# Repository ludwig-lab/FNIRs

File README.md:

# FNIRs
This project aims to create a FNIRs device that will connect directly to the TDT. The current circuit boards in this repository include as follows:
Detector: This board includes a photodiode sensor, and an amplifier.
Emitter: This board contains 3 different LED types, one is IR, one is red, and one is a bicolor LED with both IR and red light. This board is for testing to see which LED or LED combination we should use.
Port: This will plug into the TDT Subject Interface Module.

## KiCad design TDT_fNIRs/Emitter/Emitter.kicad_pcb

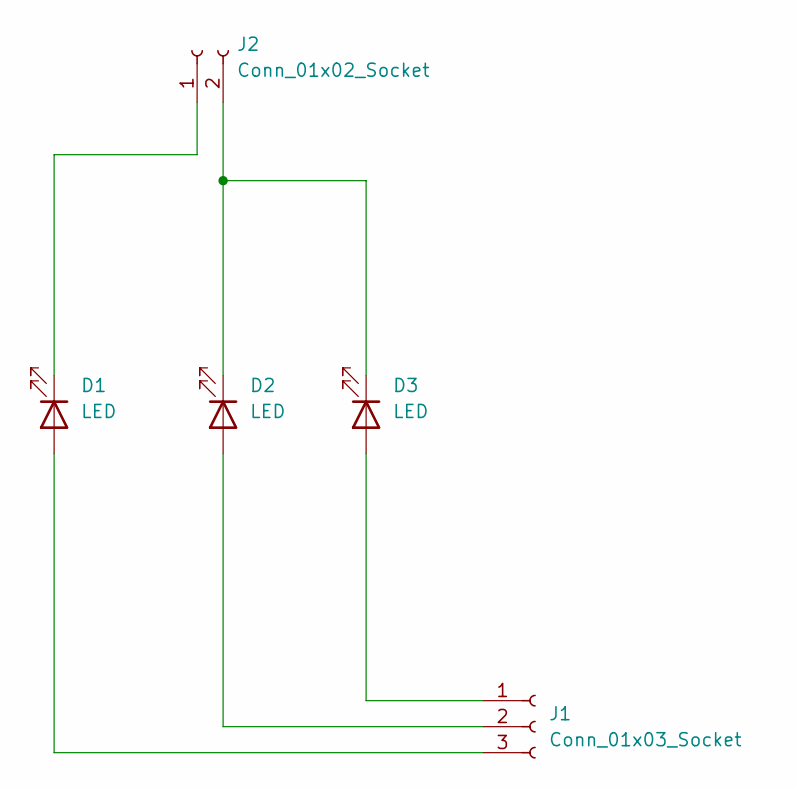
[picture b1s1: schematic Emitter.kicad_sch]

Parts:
D1: LED; BiColorLED
D2: LED; LEDIR
D3: LED; LEDR
J1: Conn_01x03_Socket; PinSocket_1x03_P2.54mm_Vertical
J2: Conn_01x02_Socket; PinSocket_1x02_P2.54mm_Vertical

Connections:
unnamed: D1.2 (A), J1.3
unnamed: D1.1 (K), J2.1
unnamed: D2.2 (A), J1.2
unnamed: D2.1 (K), D3.1 (A), J2.2
unnamed: D3.2 (K), J1.1

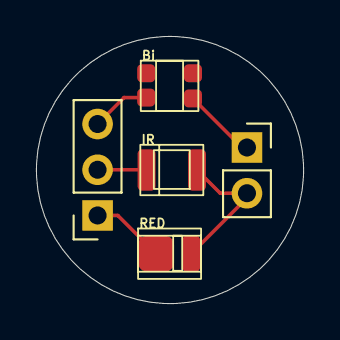
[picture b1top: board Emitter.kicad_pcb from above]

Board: 2 copper layers, 14.8 x 14.8 mm, 5 parts (0 on the bottom side), 5 nets.

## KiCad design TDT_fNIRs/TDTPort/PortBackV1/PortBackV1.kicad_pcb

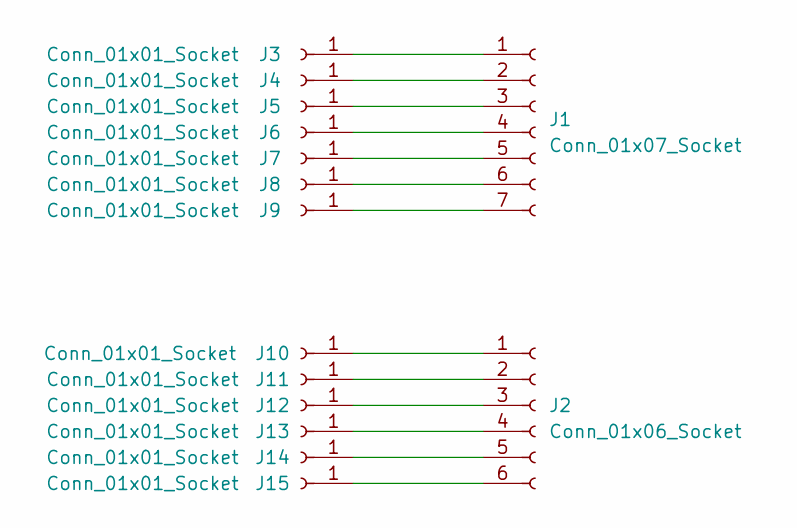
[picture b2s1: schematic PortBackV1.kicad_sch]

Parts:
J1: Conn_01x07_Socket; PinSocket_1x07_P2.54mm_Vertical
J2: Conn_01x06_Socket; PinSocket_1x06_P2.54mm_Vertical
J3, J4, J5, J6, J7, J8, J9, J10, J11, J12, J13, J14, J15: Conn_01x01_Socket; PinHeader_1x01_P1.00mm_Vertical

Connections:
unnamed: J1.1, J3.1
unnamed: J1.2, J4.1
unnamed: J1.3, J5.1
unnamed: J1.4, J6.1
unnamed: J1.5, J7.1
unnamed: J1.6, J8.1
unnamed: J1.7, J9.1
unnamed: J2.1, J10.1
unnamed: J2.2, J11.1
unnamed: J2.3, J12.1
unnamed: J2.4, J13.1
unnamed: J2.5, J14.1
unnamed: J2.6, J15.1

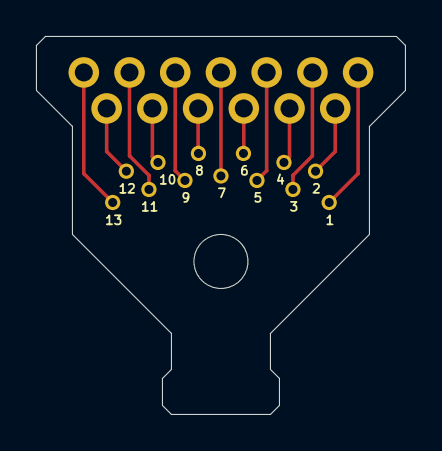
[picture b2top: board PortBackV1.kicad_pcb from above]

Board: 2 copper layers, 20.5 x 21.0 mm, 15 parts (0 on the bottom side), 13 nets.

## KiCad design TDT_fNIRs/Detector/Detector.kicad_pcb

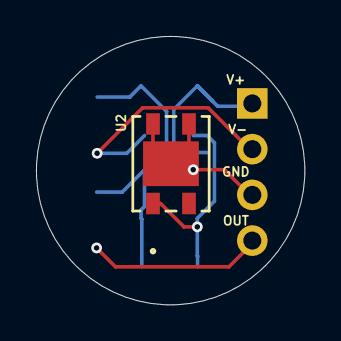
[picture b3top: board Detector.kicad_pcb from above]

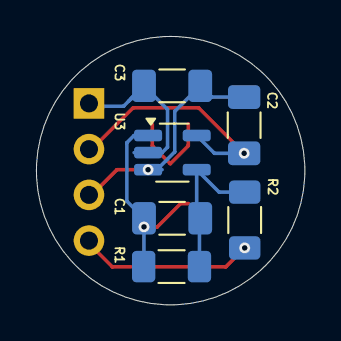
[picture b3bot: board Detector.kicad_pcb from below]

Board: 2 copper layers, 14.9 x 14.9 mm, 8 parts (6 on the bottom side), 6 nets.

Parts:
C1, C2, C3: C; C_1206_3216Metric_Pad1.33x1.80mm_HandSolder
R1, R2: R_US; R_1206_3216Metric_Pad1.30x1.75mm_HandSolder
U2: VEMD5060X01; SMD_VEMD5-5X4_VIS
U3: OPA376xxDCK; SOT-23-5_HandSoldering
V+: Conn_01x04_Socket; PinSocket_1x04_P2.54mm_Vertical

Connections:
unnamed: C1.2, R1.2, R2.1, U3.4
unnamed: C1.1, R1.1, U2.1 (ANODE), U3.1 (+)
Vneg: C2.1, U3.5 (V+), V+.2
Vpos: C3.1, U3.2 (V-), V+.1
gnd: C2.2, C3.2, U2.3 (CATHODE), U2.4 (CATHODE), U2.5 (CATHODE), U3.3 (-), V+.3
output: R2.2, V+.4

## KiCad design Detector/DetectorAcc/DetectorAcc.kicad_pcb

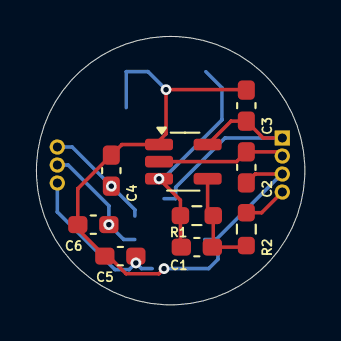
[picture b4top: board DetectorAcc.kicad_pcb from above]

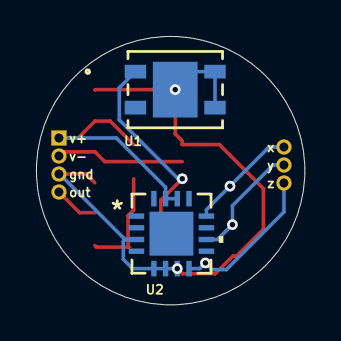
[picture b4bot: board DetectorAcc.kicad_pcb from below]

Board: 2 copper layers, 14.9 x 14.9 mm, 13 parts (2 on the bottom side), 9 nets.

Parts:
C1, C2, C3, C4, C5, C6: C; C_0603_1608Metric_Pad1.08x0.95mm_HandSolder
J1: Conn_01x04_Socket; PinSocket_1x04_P1.00mm_Vertical
J2: Conn_01x03_Socket; PinSocket_1x03_P1.00mm_Vertical
R1, R2: R_US; R_0603_1608Metric_Pad0.98x0.95mm_HandSolder
U1: OPA376xxDCK; SOT-23-5_HandSoldering
U2: VEMD5060X01; SMD_VEMD5-5X4_VIS
U3: ADXL325BCPZ; CP_16_5A_ADI

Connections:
unnamed: C1.2, R1.2, R2.1, U1.4
unnamed: C1.1, R1.1, U1.3 (-), U2.1 (ANODE)
Vneg: C2.1, J1.2, U1.2 (V-)
Vpos: C3.1, J1.1, U1.5 (V+), U3.14 (VS), U3.15 (VS)
gnd: C2.2, C3.2, C4.1, C5.2, C6.2, J1.3, U1.1 (+), U2.3 (CATHODE), U2.4 (CATHODE), U2.5 (CATHODE), U3.3 (COM), U3.5 (COM), U3.6 (COM), U3.7 (COM)
output: J1.4, R2.2
xout: C4.2, J2.1, U3.12 (XOUT)
yout: C6.1, J2.2, U3.10 (YOUT)
zout: C5.1, J2.3, U3.8 (ZOUT)

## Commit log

2025-09-03 Add files via upload
    Detector with Accelerometer
2025-09-03 Create DetectorV1
2025-09-03 Add files via upload
    File for JLCPCB Ordering
2026-02-09 Restructure project folder to include fNIRs analysis
2026-02-09 Added flexNIRs functions and test scripts
2026-02-11 Added fNIRs class
2026-02-16 Updated fNIRs class, added ECG analysis
2026-02-16 Updated analysis scripts
2026-02-16 Updated scripts
